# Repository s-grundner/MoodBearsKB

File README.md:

# Custom Keyboard

Personalized Totem Keyboard: PCB and Case Completely reworked.

Inspirations:

- [TOTEM Keyboard](https://github.com/GEIGEIGEIST/TOTEM)

## Revision 1

Revision 1 is focused on using parts i have at home. This impedes the case design a little bit though, as the THT diodes intersect with the Original switch plate

|  |  |
| :--------------------: | :------------------------: |
|    Keyboard Preview    |             PCB            |

```text
// Template 
//             ┏━━━━━━━━━━━┳━━━━━━━━━━━┳━━━━━━━━━━━┳━━━━━━━━━━━┳━━━━━━━━━━━┓   ┏━━━━━━━━━━━┳━━━━━━━━━━━┳━━━━━━━━━━━┳━━━━━━━━━━━┳━━━━━━━━━━━┓
//             ┃           ┃           ┃           ┃           ┃           ┃   ┃           ┃           ┃           ┃           ┃           ┃
// ┏━━━━━━━━━━━╋━━━━━━━━━━━╋━━━━━━━━━━━╋━━━━━━━━━━━╋━━━━━━━━━━━╋━━━━━━━━━━━┫   ┣━━━━━━━━━━━╋━━━━━━━━━━━╋━━━━━━━━━━━╋━━━━━━━━━━━╋━━━━━━━━━━━╋━━━━━━━━━━━┓
// ┃    ESC    ┃           ┃    ALT    ┃   CTRL    ┃   SHIFT   ┃           ┃   ┃           ┃   SHIFT   ┃   CTRL    ┃    ALT    ┃           ┃   BSPC    ┃
// ┣━━━━━━━━━━━╋━━━━━━━━━━━╋━━━━━━━━━━━╋━━━━━━━━━━━╋━━━━━━━━━━━╋━━━━━━━━━━━┫   ┣━━━━━━━━━━━╋━━━━━━━━━━━╋━━━━━━━━━━━╋━━━━━━━━━━━╋━━━━━━━━━━━╋━━━━━━━━━━━┫
// ┃    TAB    ┃           ┃           ┃           ┃           ┃           ┃   ┃           ┃           ┃           ┃           ┃           ┃   ENTER   ┃
// ┗━━━━━━━━━━━┻━━━━━━━━━━━┻━━━━━━━━━━━╋━━━━━━━━━━━╋━━━━━━━━━━━╋━━━━━━━━━━━┫   ┣━━━━━━━━━━━╋━━━━━━━━━━━╋━━━━━━━━━━━╋━━━━━━━━━━━┻━━━━━━━━━━━┻━━━━━━━━━━━┛
//                                     ┃   SUPER   ┃    SYM    ┃    SPC    ┃   ┃    SPC    ┃    NUM    ┃    DEL    ┃
//                                     ┗━━━━━━━━━━━┻━━━━━━━━━━━┻━━━━━━━━━━━┛   ┗━━━━━━━━━━━┻━━━━━━━━━━━┻━━━━━━━━━━━┛
```

## Firmware Update

1. Flash settings_reset to dongle, left, and right.
2. Reboot/power-cycle all three devices.
3. Flash normal firmware to dongle first.
4. Reboot dongle.
5. Flash normal firmware to left and right.
6. Reboot each half again.
7. Wait for the halves to pair to the dongle.

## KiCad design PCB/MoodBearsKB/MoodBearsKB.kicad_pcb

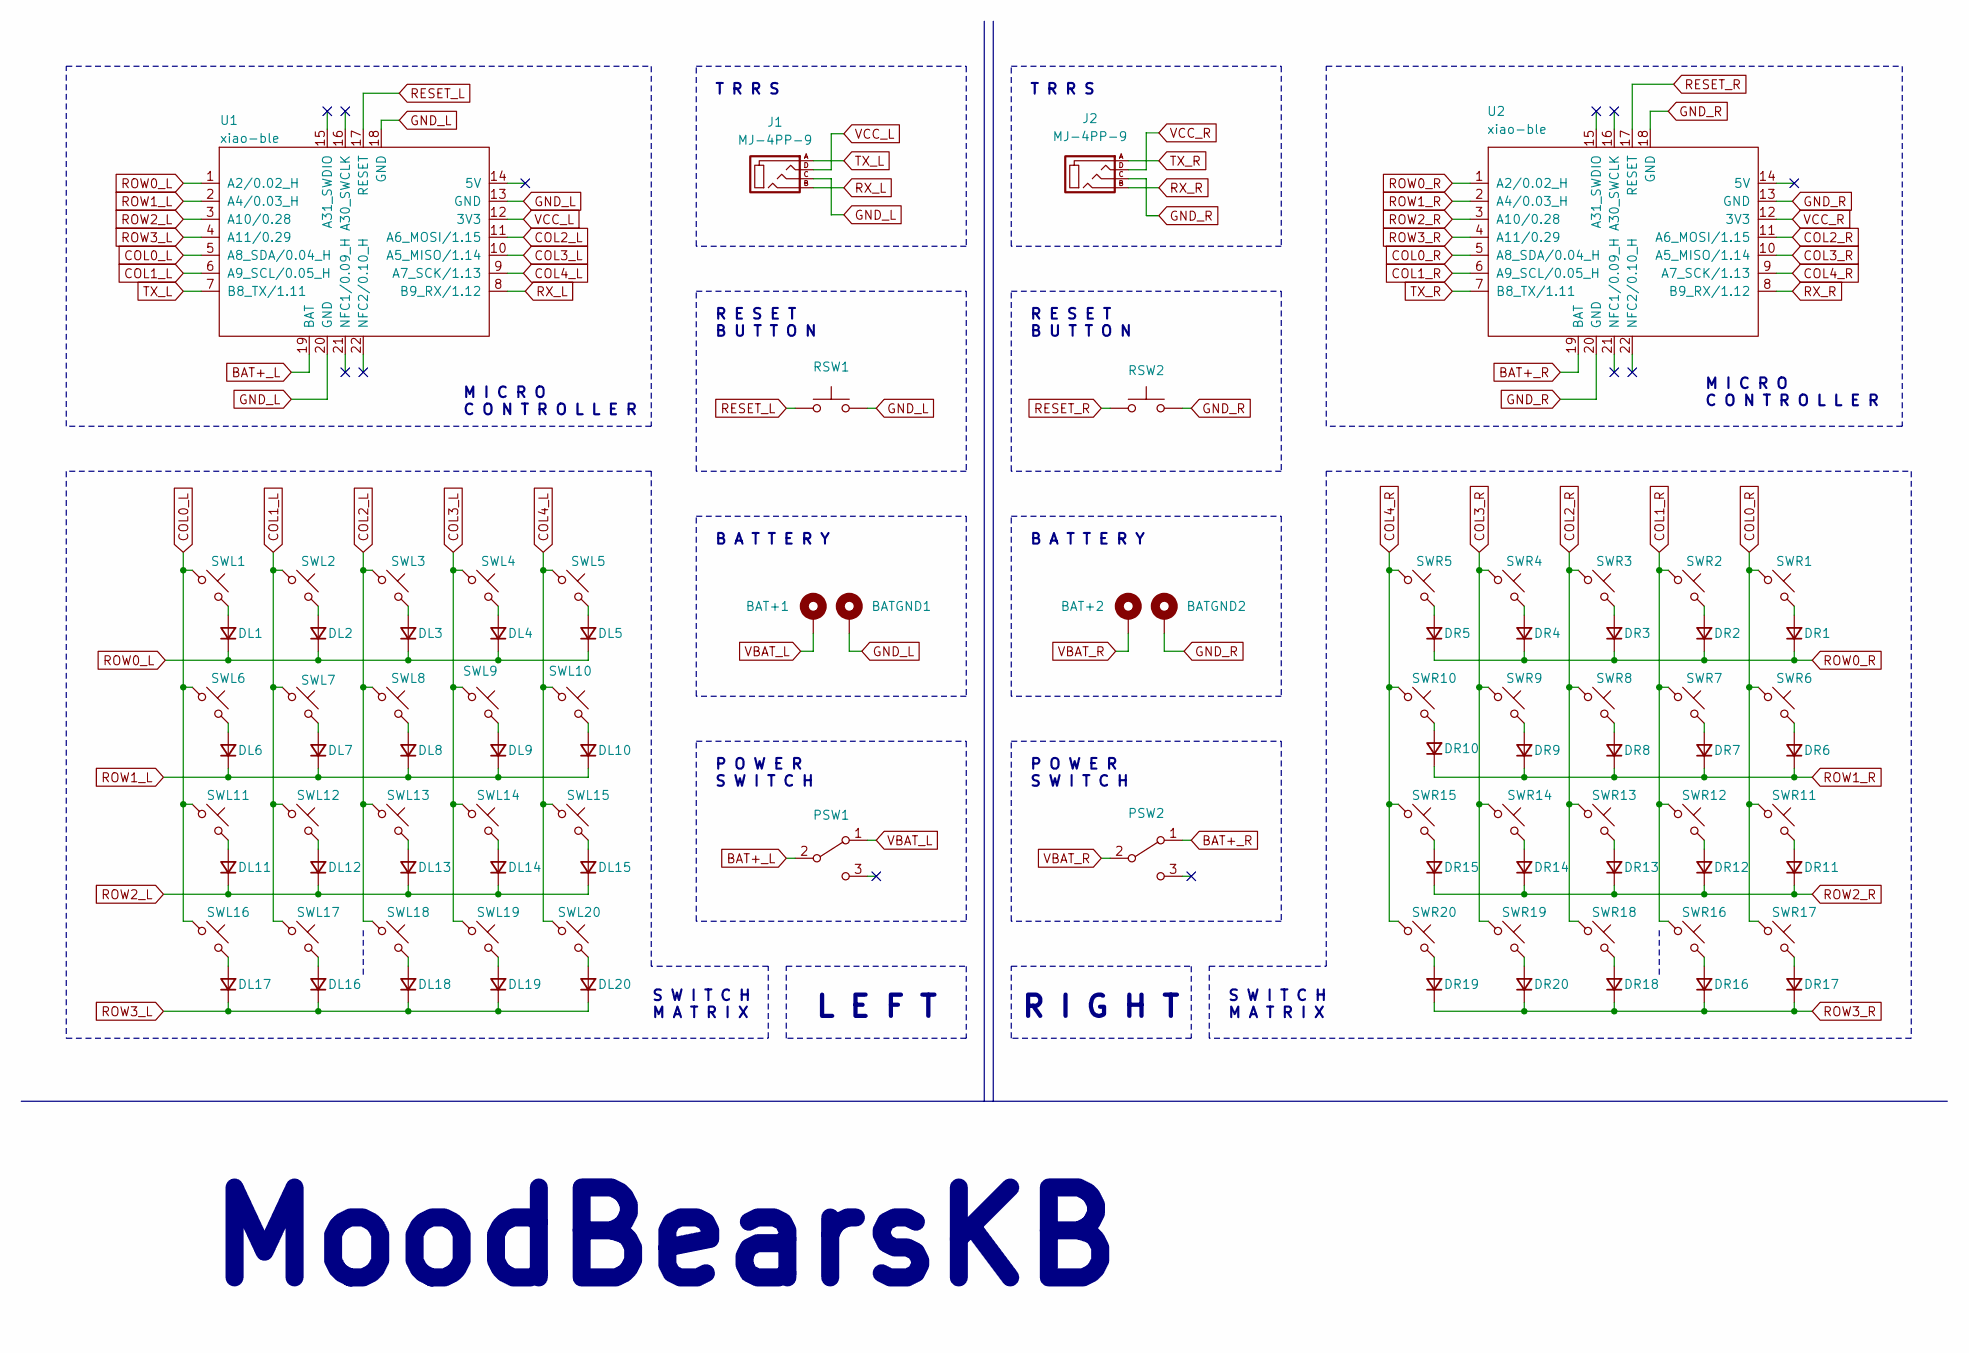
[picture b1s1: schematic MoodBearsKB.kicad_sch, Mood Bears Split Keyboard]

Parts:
BAT+1, BAT+2: +; BatteryPad
BATGND1, BATGND2: -; BatteryPad
DL1, DL2, DL3, DL4, DL5, DL6, DL7, DL8, DL9, DL10, DL11, DL12, DL13, DL14, DL15, DL16, DL17, DL18, DL19, DL20: D_Small; Diode_SOD27
DR1, DR2, DR3, DR4, DR5, DR6, DR7, DR8, DR9, DR10, DR11, DR12, DR13, DR14, DR15, DR16, DR17, DR18, DR19, DR20: D_Small; Diode_SOD27
J1, J2: MJ-4PP-9; MJ-4PP-9_1side
PSW1, PSW2: SW_SPDT; MSK12C02
RSW1, RSW2: SW_Push; SKHLLCA010
SWL1, SWL2, SWL3, SWL4, SWL5, SWL6, SWL7, SWL8, SWL9, SWL10, SWL11, SWL12, SWL13, SWL14, SWL15, SWL16, SWL17, SWL18, SWL19, SWL20: SW_Push_45deg; Kailh_socket_PG1350_optional
SWR1, SWR2, SWR3, SWR4, SWR5, SWR6, SWR7, SWR8, SWR9, SWR10, SWR11, SWR12, SWR13, SWR14, SWR15, SWR16, SWR17, SWR18, SWR19, SWR20: SW_Push_45deg; Kailh_socket_PG1350_optional
U1, U2: xiao-ble; xiao-ble-smd-cutout

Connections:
BAT+_L: PSW1.2 (B), U1.19 (BAT)
BAT+_R: PSW2.1 (A), U2.19 (BAT)
COL0_L: SWL1.1, SWL6.1, SWL11.1, SWL16.1, U1.5 (A8_SDA/0.04_H)
COL0_R: SWR1.1, SWR6.1, SWR11.1, SWR17.1, U2.5 (A8_SDA/0.04_H)
COL1_L: SWL2.1, SWL7.1, SWL12.1, SWL17.1, U1.6 (A9_SCL/0.05_H)
COL1_R: SWR2.1, SWR7.1, SWR12.1, SWR16.1, U2.6 (A9_SCL/0.05_H)
COL2_L: SWL3.1, SWL8.1, SWL13.1, SWL18.1, U1.11 (A6_MOSI/1.15)
COL2_R: SWR3.1, SWR8.1, SWR13.1, SWR18.1, U2.11 (A6_MOSI/1.15)
COL3_L: SWL4.1, SWL9.1, SWL14.1, SWL19.1, U1.10 (A5_MISO/1.14)
COL3_R: SWR4.1, SWR9.1, SWR14.1, SWR19.1, U2.10 (A5_MISO/1.14)
COL4_L: SWL5.1, SWL10.1, SWL15.1, SWL20.1, U1.9 (A7_SCK/1.13)
COL4_R: SWR5.1, SWR10.1, SWR15.1, SWR20.1, U2.9 (A7_SCK/1.13)
GND_L: BATGND1.1, J1.C, RSW1.1, U1.13 (GND), U1.18 (GND), U1.20 (GND)
GND_R: BATGND2.1, J2.C, RSW2.2, U2.13 (GND), U2.18 (GND), U2.20 (GND)
unnamed: DL1.2 (A), SWL1.2
unnamed: DL2.2 (A), SWL2.2
unnamed: DL3.2 (A), SWL3.2
unnamed: DL4.2 (A), SWL4.2
unnamed: DL5.2 (A), SWL5.2
unnamed: DL6.2 (A), SWL6.2
unnamed: DL7.2 (A), SWL7.2
unnamed: DL8.2 (A), SWL8.2
unnamed: DL9.2 (A), SWL9.2
unnamed: DL10.2 (A), SWL10.2
unnamed: DL11.2 (A), SWL11.2
unnamed: DL12.2 (A), SWL12.2
unnamed: DL13.2 (A), SWL13.2
unnamed: DL14.2 (A), SWL14.2
unnamed: DL15.2 (A), SWL15.2
unnamed: DL16.2 (A), SWL17.2
unnamed: DL17.2 (A), SWL16.2
unnamed: DL18.2 (A), SWL18.2
unnamed: DL19.2 (A), SWL19.2
unnamed: DL20.2 (A), SWL20.2
unnamed: DR1.2 (A), SWR1.2
unnamed: DR2.2 (A), SWR2.2
unnamed: DR3.2 (A), SWR3.2
unnamed: DR4.2 (A), SWR4.2
unnamed: DR5.2 (A), SWR5.2
unnamed: DR6.2 (A), SWR6.2
unnamed: DR7.2 (A), SWR7.2
unnamed: DR8.2 (A), SWR8.2
unnamed: DR9.2 (A), SWR9.2
unnamed: DR10.2 (A), SWR10.2
unnamed: DR11.2 (A), SWR11.2
unnamed: DR12.2 (A), SWR12.2
unnamed: DR13.2 (A), SWR13.2
unnamed: DR14.2 (A), SWR14.2
unnamed: DR15.2 (A), SWR15.2
unnamed: DR16.2 (A), SWR16.2
unnamed: DR17.2 (A), SWR17.2
unnamed: DR18.2 (A), SWR18.2
unnamed: DR19.2 (A), SWR20.2
unnamed: DR20.2 (A), SWR19.2
RESET_L: RSW1.2, U1.17 (RESET)
RESET_R: RSW2.1, U2.17 (RESET)
ROW0_L: DL1.1 (K), DL2.1 (K), DL3.1 (K), DL4.1 (K), DL5.1 (K), U1.1 (A2/0.02_H)
ROW0_R: DR1.1 (K), DR2.1 (K), DR3.1 (K), DR4.1 (K), DR5.1 (K), U2.1 (A2/0.02_H)
ROW1_L: DL6.1 (K), DL7.1 (K), DL8.1 (K), DL9.1 (K), DL10.1 (K), U1.2 (A4/0.03_H)
ROW1_R: DR6.1 (K), DR7.1 (K), DR8.1 (K), DR9.1 (K), DR10.1 (K), U2.2 (A4/0.03_H)
ROW2_L: DL11.1 (K), DL12.1 (K), DL13.1 (K), DL14.1 (K), DL15.1 (K), U1.3 (A10/0.28)
ROW2_R: DR11.1 (K), DR12.1 (K), DR13.1 (K), DR14.1 (K), DR15.1 (K), U2.3 (A10/0.28)
ROW3_L: DL16.1 (K), DL17.1 (K), DL18.1 (K), DL19.1 (K), DL20.1 (K), U1.4 (A11/0.29)
ROW3_R: DR16.1 (K), DR17.1 (K), DR18.1 (K), DR19.1 (K), DR20.1 (K), U2.4 (A11/0.29)
RX_L: J1.B, U1.8 (B9_RX/1.12)
RX_R: J2.B, U2.8 (B9_RX/1.12)
TX_L: J1.A, U1.7 (B8_TX/1.11)
TX_R: J2.A, U2.7 (B8_TX/1.11)
VBAT_L: BAT+1.1, PSW1.1 (A)
VBAT_R: BAT+2.1, PSW2.2 (B)
VCC_L: J1.D, U1.12 (3V3)
VCC_R: J2.D, U2.12 (3V3)

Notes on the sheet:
M I C R O C O N T R O L L E R
T R R S
R E S E T B U T T O N
S W I T C H M A T R I X
P O W E R S W I T C H
MoodBearsKB
B A T T E R Y
R I G H T
L E F T

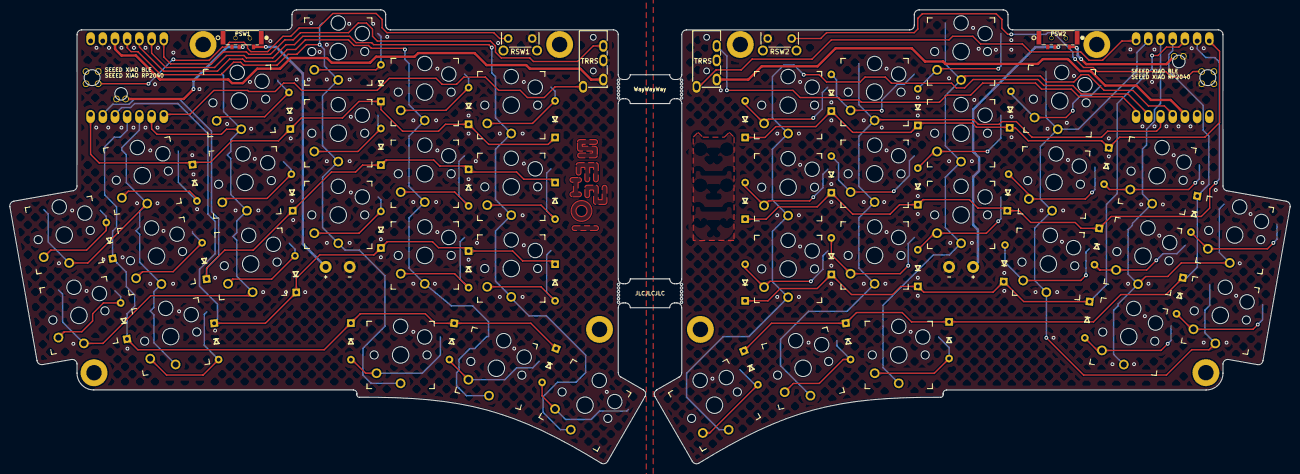
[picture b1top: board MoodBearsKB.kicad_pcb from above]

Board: 2 copper layers, 266.5 x 94.5 mm, 92 parts (0 on the bottom side), 72 nets.

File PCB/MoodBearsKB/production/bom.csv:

Designator,Footprint,Quantity,Value,LCSC Part #
"BAT+1, BAT+2",BatteryPad,2,+,
"BATGND1, BATGND2",BatteryPad,2,-,
"DL1, DL10, DL11, DL12, DL13, DL14, DL15, DL16, DL17, DL18, DL19, DL2, DL20, DL3, DL4, DL5, DL6, DL7, DL8, DL9, DR1, DR10, DR11, DR12, DR13, DR14, DR15, DR16, DR17, DR18, DR19, DR2, DR20, DR3, DR4, DR5, DR6, DR7, DR8, DR9",Diode_SOD27,40,D_Small,
"J1, J2",MJ-4PP-9_1side,2,MJ-4PP-9,
"PSW1, PSW2",MSK12C02,2,SW_SPDT,
"RSW1, RSW2",SW_Tactile_SPST_Angled_PTS645Vx39-2LFS,2,SW_Push,
"SWL1, SWL10, SWL11, SWL12, SWL13, SWL14, SWL15, SWL16, SWL17, SWL18, SWL19, SWL2, SWL20, SWL3, SWL4, SWL5, SWL6, SWL7, SWL8, SWL9, SWR1, SWR10, SWR11, SWR12, SWR13, SWR14, SWR15, SWR16, SWR17, SWR18, SWR19, SWR2, SWR20, SWR3, SWR4, SWR5, SWR6, SWR7, SWR8, SWR9",Kailh_socket_PG1350_optional,40,SW_Push_45deg,
"U1, U2",xiao-ble-smd-cutout,2,xiao-ble,

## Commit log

2025-06-15 initial commit - ready for prod
2025-06-15 cleared README
2025-06-15 added pcbway Prod Files and specified order number location
2025-06-18 sent to PCBWay!
2025-06-18 Edit Schematic Footer
2025-06-18 added documentation for schem and layout as pdf
2025-06-28 upd docs
2025-08-02 ZMK Firmware Added
2025-08-02 Action
2025-08-02 Configured Layout
2025-08-02 test base
2025-08-02 test sym
2025-08-02 test num
2025-08-02 Added Dongle
2025-08-02 added locale module
2025-08-02 Full DE Layout and nav layer
2025-08-02 added nav layer
2025-08-02 upd keymap
2025-08-02 added accessible super key in num layer
2025-08-02 nav layer key on other side for one hand navigation
2025-08-02 added caps word on lt tab
2025-08-02 enter on thumb cluster
2025-08-02 fixed caps word
2025-09-21 tweaks for navigating file system (~/)
2025-09-21 try fixing the caps word key
2025-09-21 nav layer testing
2025-09-23 added caps
2025-10-22 Add DeepWiki badge to README
    Added a badge link for DeepWiki to the README.
2026-06-29 Rename board from seeeduino_xiao_ble to xiao_ble
2026-06-30 stls and firmware
2026-06-30 firmware
2026-06-30 upload instructions
2026-06-30 battery level reporing
